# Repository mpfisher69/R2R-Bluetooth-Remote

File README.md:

<h1> Bluetooth Remote Controller</h1>
<p>For Reel-to-Reel tape recorders and vintage cassette decks.</p>
<p>Works with any open-reel (reel-to-reel) tape deck equipped with remote control connector, with active-low inputs</p>
It replicates functionality of original Technics remote controllers such as RP-9690 and RP-070 (including reverse-play function).</br>
Connects to remote controller input on Technics RS1500, RS1506 and RS1700 and also on Akai GX-635, GX-636, GX-747, GX-747DBX, GX-77 and also vintage cassette decks.</br>
This Bluetooth remote can be wired to other makes and models of tape machines, as long as they are equipped with a "tactile" tape transport buttons and "active-low" logic, such as Pioneer RT909.</p>

<p>Screenshots:<br>
<br>

</p>
<p> I have some of the receivers fully built, if you don't want to build one yourself.<br>
Please <a href="mailto:audio@mpfisher.com">contact me</a> for details.<br>

</p>

<p>Software is provided "as is" without any guarantee. I am looking for a colaborators who would want to develop it further and also help develop iOS app for iPhone/iPad.</p>
<p>To-Do:

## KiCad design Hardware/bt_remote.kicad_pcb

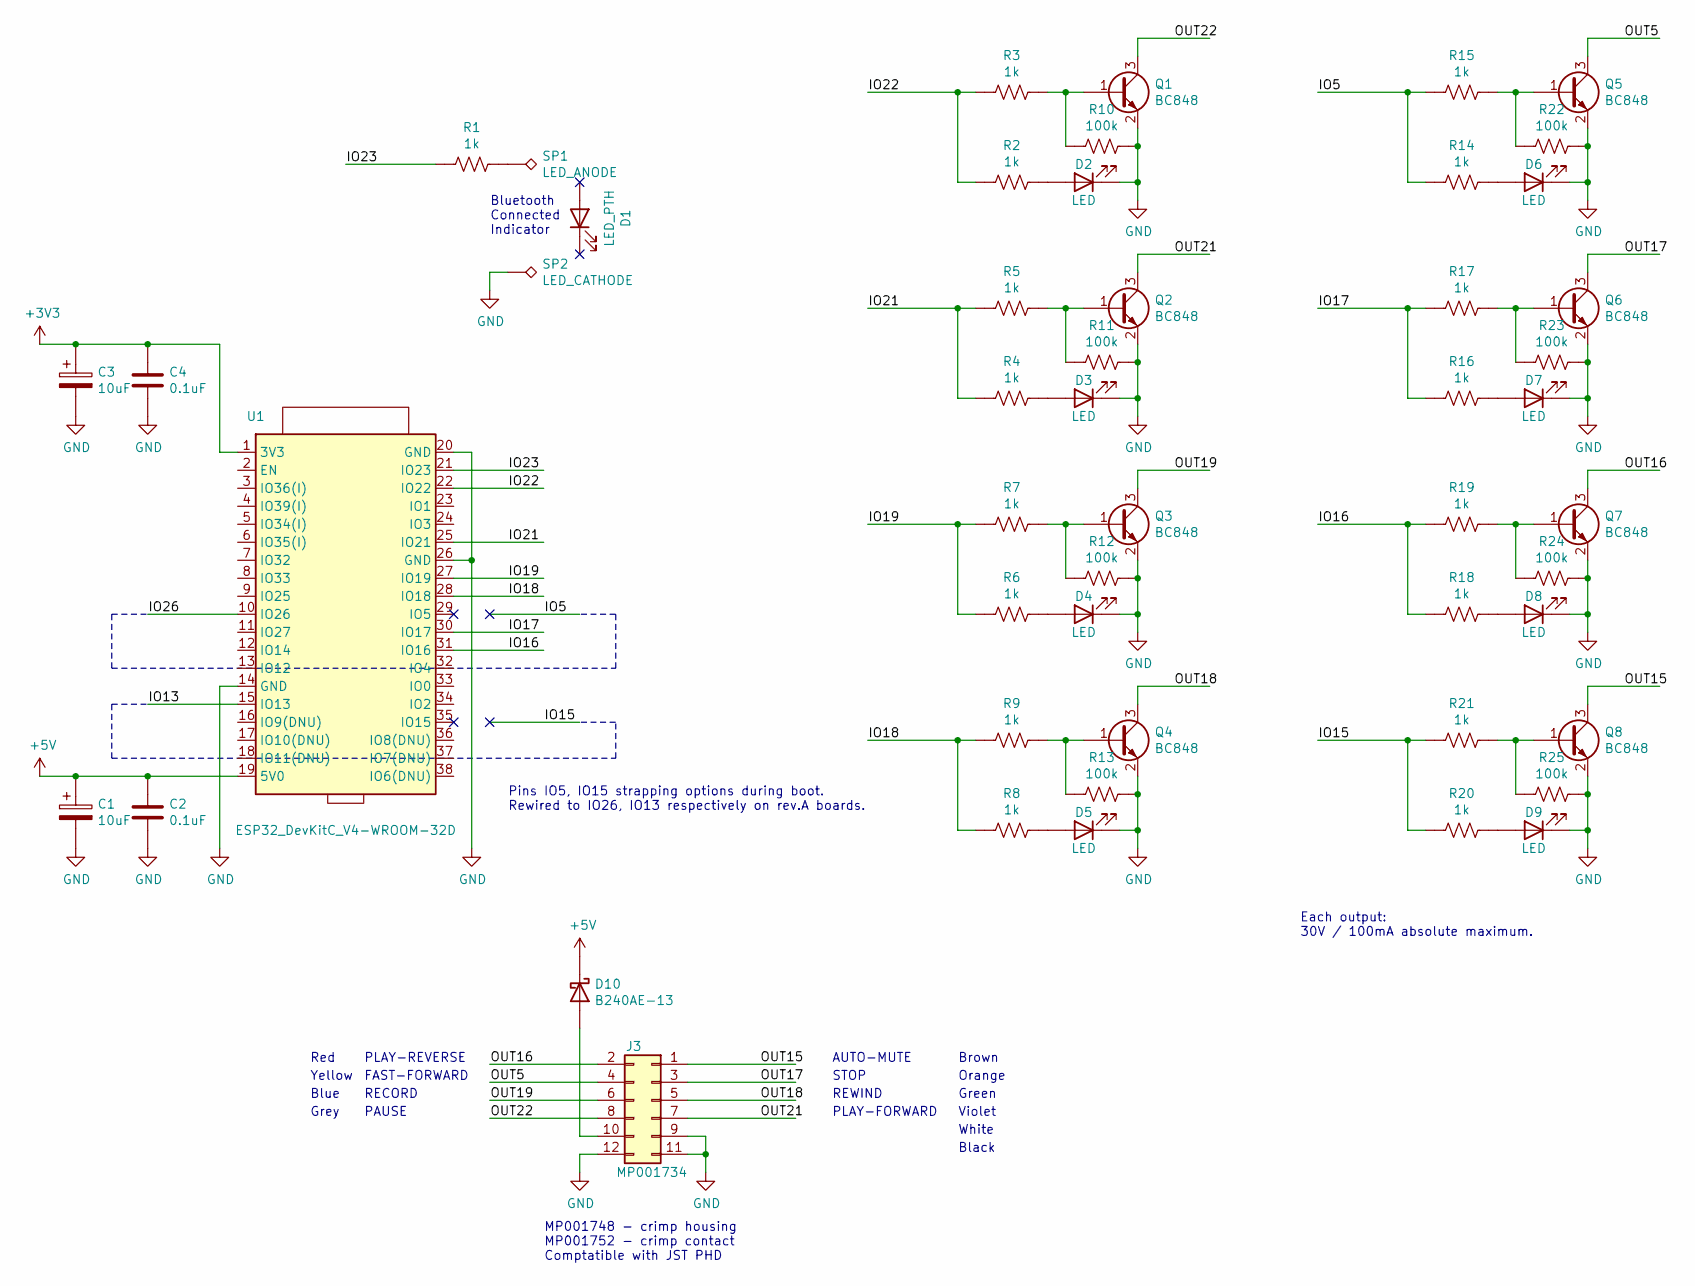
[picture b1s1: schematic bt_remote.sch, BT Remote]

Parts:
C1, C3: 10uF; CP_Radial_D5.0mm_P2.50mm
C2, C4: 0.1uF; C_0805_2012Metric
D1: LED_PTH
D2, D3, D4, D5, D6, D7, D8, D9: LED; LED_0805_2012Metric
D10: B240AE-13; D_SMA
J3: MP001734; JST_PHD_B12B-PHDSS_2x06_P2.00mm_Vertical
Q1, Q2, Q3, Q4, Q5, Q6, Q7, Q8: BC848; SOT-23
R1, R2, R3, R4, R5, R6, R7, R8, R9, R14, R15, R16, R17, R18, R19, R20, R21: 1k; R_0603_1608Metric
R10, R11, R12, R13, R22, R23, R24, R25: 100k; R_0603_1608Metric
SP1: LED_ANODE; TestPoint_THTPad_D2.0mm_Drill1.0mm
SP2: LED_CATHODE; TestPoint_THTPad_2.0x2.0mm_Drill1.0mm
U1: ESP32_DevKitC_V4-WROOM-32D; ESP32-DevKitC_v4

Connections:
+3V3: C3.1, C4.1, U1.1 (3V3)
+5V: C1.1, C2.1, D10.1 (K), U1.19 (5V0)
/IO5: R14.2, R15.2, U1.29 (IO5)
/IO15: R20.2, R21.2, U1.35 (IO15)
/IO16: R18.2, R19.2, U1.31 (IO16)
/IO17: R16.2, R17.2, U1.30 (IO17)
/IO18: R8.2, R9.2, U1.28 (IO18)
/IO19: R6.2, R7.2, U1.27 (IO19)
/IO21: R4.2, R5.2, U1.25 (IO21)
/IO22: R2.2, R3.2, U1.22 (IO22)
/IO23: R1.2, U1.21 (IO23)
/OUT5: J3.4, Q5.3 (C)
/OUT15: J3.1, Q8.3 (C)
/OUT16: J3.2, Q7.3 (C)
/OUT17: J3.3, Q6.3 (C)
/OUT18: J3.5, Q4.3 (C)
/OUT19: J3.6, Q3.3 (C)
/OUT21: J3.7, Q2.3 (C)
/OUT22: J3.8, Q1.3 (C)
GND: C1.2, C2.2, C3.2, C4.2, D2.1 (K), D3.1 (K), D4.1 (K), D5.1 (K), D6.1 (K), D7.1 (K), D8.1 (K), D9.1 (K), J3.9, J3.11, J3.12, Q1.2 (E), Q2.2 (E), Q3.2 (E), Q4.2 (E), Q5.2 (E), Q6.2 (E), Q7.2 (E), Q8.2 (E), R10.1, R11.1, R12.1, R13.1, R22.1, R23.1, R24.1, R25.1, SP2.1, U1.14 (GND), U1.20 (GND), U1.26 (GND)
unnamed: D2.2 (A), R2.1
unnamed: D3.2 (A), R4.1
unnamed: D4.2 (A), R6.1
unnamed: D5.2 (A), R8.1
unnamed: D6.2 (A), R14.1
unnamed: D7.2 (A), R16.1
unnamed: D8.2 (A), R18.1
unnamed: D9.2 (A), R20.1
unnamed: D10.2 (A), J3.10
unnamed: Q1.1 (B), R3.1, R10.2
unnamed: Q2.1 (B), R5.1, R11.2
unnamed: Q3.1 (B), R7.1, R12.2
unnamed: Q4.1 (B), R9.1, R13.2
unnamed: Q5.1 (B), R15.1, R22.2
unnamed: Q6.1 (B), R17.1, R23.2
unnamed: Q7.1 (B), R19.1, R24.2
unnamed: Q8.1 (B), R21.1, R25.2
unnamed: R1.1, SP1.1

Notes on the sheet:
PLAY-REVERSE
STOP
REWIND
FAST-FORWARD
PAUSE
PLAY-FORWARD
RECORD
AUTO-MUTE
Bluetooth Connected Indicator
MP001748 - crimp housing MP001752 - crimp contact Comptatible with JST PHD
Each output: 30V / 100mA absolute maximum.
Green
Violet
Brown
Orange
Red
Yellow
Grey
Blue
White
Black
Pins IO5, IO15 strapping options during boot. Rewired to IO26, IO13 respectively on rev.A boards.

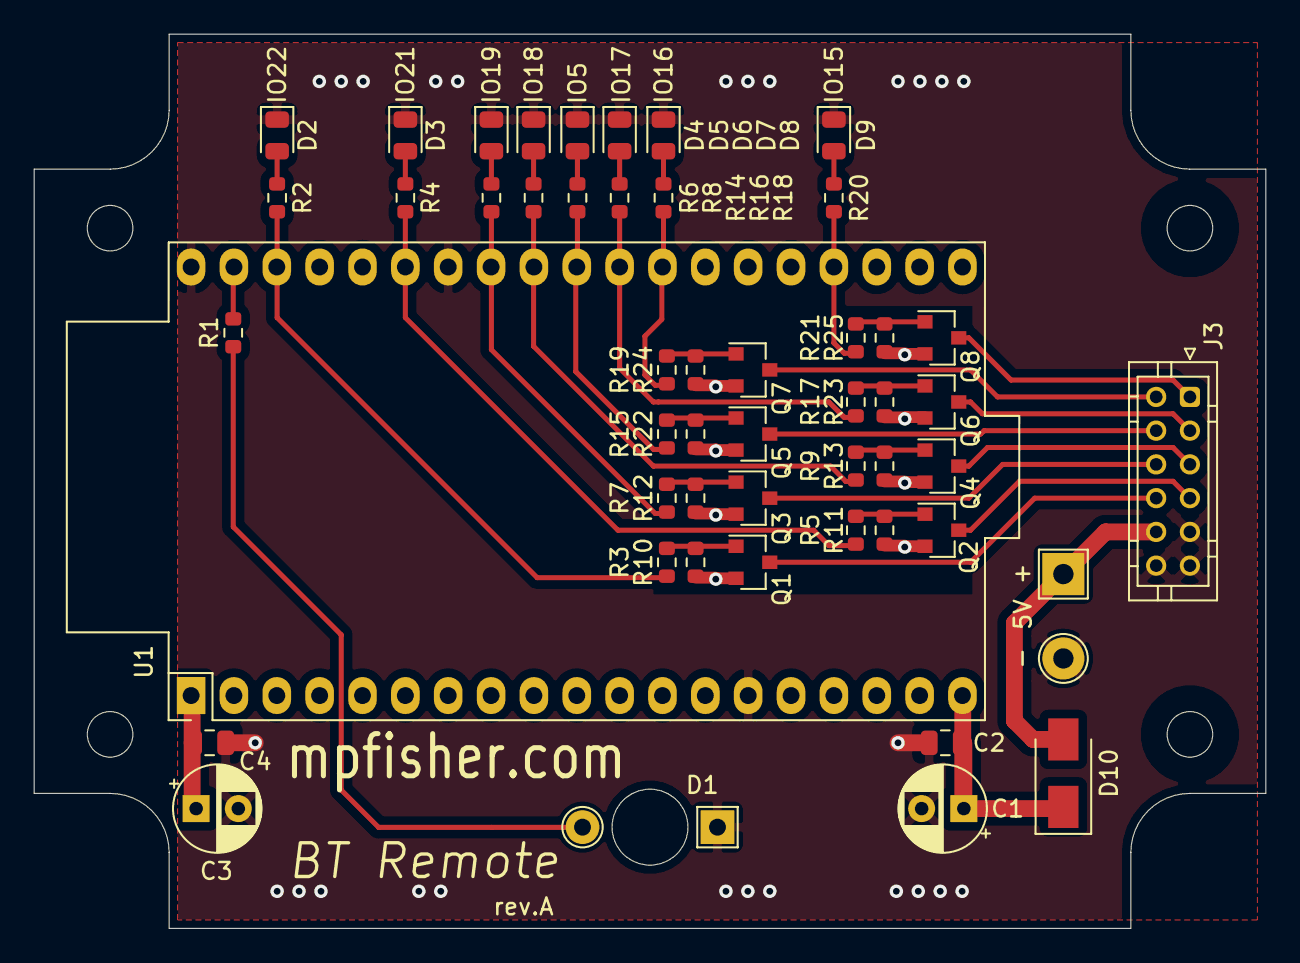
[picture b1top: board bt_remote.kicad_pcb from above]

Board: 2 copper layers, 73.0 x 53.0 mm, 50 parts (0 on the bottom side), 38 nets.

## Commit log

2021-07-04 README.md updates
    Initial README.md updates.
2021-11-20 full commit
    Committing the entire project.
2021-11-20 added user guides
